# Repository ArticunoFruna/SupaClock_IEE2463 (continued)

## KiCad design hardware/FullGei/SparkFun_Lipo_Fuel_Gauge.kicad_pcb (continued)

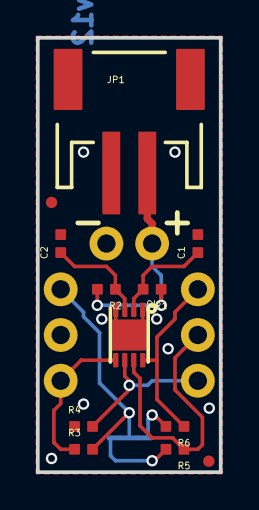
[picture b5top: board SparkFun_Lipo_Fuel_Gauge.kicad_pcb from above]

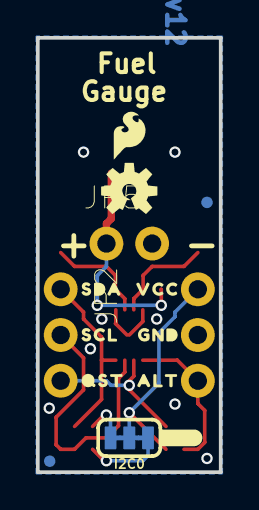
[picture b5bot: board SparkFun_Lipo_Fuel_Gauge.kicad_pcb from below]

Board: 2 copper layers, 10.2 x 24.1 mm, 29 parts (15 on the bottom side), 11 nets.

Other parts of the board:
U$2: SDA0
U$3: SCL0
U$4: QST0
U$5: VCC0
U$6: GND0
U$7: ALT0
U$8: #I2C#0

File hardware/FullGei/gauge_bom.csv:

"Reference","Value","Footprint"
"C1","1.0uF","SparkFun_Lipo_Fuel_Gauge:0402-TIGHT"
"C2","10nF","SparkFun_Lipo_Fuel_Gauge:0402-TIGHT"
"FRAME1","FRAME-LETTER","SparkFun_Lipo_Fuel_Gauge:CREATIVE_COMMONS"
"I2C0","JUMPER-SMT_3_2-NC_TRACE_SILK","SparkFun_Lipo_Fuel_Gauge:SMT-JUMPER_3_2-NC_TRACE_SILK"
"JP1","input","SparkFun_Lipo_Fuel_Gauge:JST-2-SMD"
"JP2","CONN_031X03_NO_SILK","SparkFun_Lipo_Fuel_Gauge:1X03_NO_SILK"
"JP3","SFE_LOGO_FLAME.1_INCH","SparkFun_Lipo_Fuel_Gauge:SFE_LOGO_FLAME_.1"
"JP4","CONN_031X03_NO_SILK","SparkFun_Lipo_Fuel_Gauge:1X03_NO_SILK"
"JP5","CONN_021X02_NO_SILK","SparkFun_Lipo_Fuel_Gauge:1X02_NO_SILK"
"JP6","FIDUCIALUFIDUCIAL","SparkFun_Lipo_Fuel_Gauge:FIDUCIAL-MICRO"
"JP7","FIDUCIALUFIDUCIAL","SparkFun_Lipo_Fuel_Gauge:FIDUCIAL-MICRO"
"JP8","FIDUCIALUFIDUCIAL","SparkFun_Lipo_Fuel_Gauge:FIDUCIAL-MICRO"
"JP9","FIDUCIALUFIDUCIAL","SparkFun_Lipo_Fuel_Gauge:FIDUCIAL-MICRO"
"LOGO1","SFE_LOGO_NAME_FLAMEBLANK","SparkFun_Lipo_Fuel_Gauge:BLANK"
"R1","1k","SparkFun_Lipo_Fuel_Gauge:0402-TIGHT"
"R2","100","SparkFun_Lipo_Fuel_Gauge:0402-TIGHT"
"R3","2.2k","SparkFun_Lipo_Fuel_Gauge:0402-TIGHT"
"R4","2.2k","SparkFun_Lipo_Fuel_Gauge:0402-TIGHT"
"R5","2.2k","SparkFun_Lipo_Fuel_Gauge:0402-TIGHT"
"R6","2.2k","SparkFun_Lipo_Fuel_Gauge:0402-TIGHT"
"U$1","OSHW-LOGOS","SparkFun_Lipo_Fuel_Gauge:OSHW-LOGO-S"
"U2","MAX1704X","SparkFun_Lipo_Fuel_Gauge:TDFN-8"

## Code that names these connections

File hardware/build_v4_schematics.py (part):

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U1_X, U1_Y = 160.0, 100.0
m.place("U1", "XIAO-ESP32-S3", "Seeed_Studio_XIAO_Series:XIAO-ESP32-S3-SMD", "Seeed_Studio_XIAO_Footprints:XIAO-ESP32-S3-SMD", U1_X, U1_Y)

m.label_pin("U1", "Seeed_Studio_XIAO_Series:XIAO-ESP32-S3-SMD", U1_X, U1_Y, 0, "1", "ECG_OUT")
m.label_pin("U1", "Seeed_Studio_XIAO_Series:XIAO-ESP32-S3-SMD", U1_X, U1_Y, 0, "2", "ECG_SDN")
m.label_pin("U1", "Seeed_Studio_XIAO_Series:XIAO-ESP32-S3-SMD", U1_X, U1_Y, 0, "3", "BLK_PWM")
m.label_pin("U1", "Seeed_Studio_XIAO_Series:XIAO-ESP32-S3-SMD", U1_X, U1_Y, 0, "4", "SPI_DC")
m.label_pin("U1", "Seeed_Studio_XIAO_Series:XIAO-ESP32-S3-SMD", U1_X, U1_Y, 0, "5", "I2C_SDA")
m.label_pin("U1", "Seeed_Studio_XIAO_Series:XIAO-ESP32-S3-SMD", U1_X, U1_Y, 0, "6", "I2C_SCL")
m.label_pin("U1", "Seeed_Studio_XIAO_Series:XIAO-ESP32-S3-SMD", U1_X, U1_Y, 0, "7", "BTN_NEXT")
m.label_pin("U1", "Seeed_Studio_XIAO_Series:XIAO-ESP32-S3-SMD", U1_X, U1_Y, 0, "8", "SPI_CS")
m.label_pin("U1", "Seeed_Studio_XIAO_Series:XIAO-ESP32-S3-SMD", U1_X, U1_Y, 0, "9", "SPI_SCK")
m.label_pin("U1", "Seeed_Studio_XIAO_Series:XIAO-ESP32-S3-SMD", U1_X, U1_Y, 0, "10", "BTN_SELECT")
m.label_pin("U1", "Seeed_Studio_XIAO_Series:XIAO-ESP32-S3-SMD", U1_X, U1_Y, 0, "11", "SPI_MOSI")
m.power_pin("U1", "Seeed_Studio_XIAO_Series:XIAO-ESP32-S3-SMD", U1_X, U1_Y, 0, "12", "+3V3")
m.power_pin("U1", "Seeed_Studio_XIAO_Series:XIAO-ESP32-S3-SMD", U1_X, U1_Y, 0, "13", "GND")
m.power_pin("U1", "Seeed_Studio_XIAO_Series:XIAO-ESP32-S3-SMD", U1_X, U1_Y, 0, "32", "+BATT")
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# 2. SELECT button (SW1) & NEXT button (SW2)
SW1_X, SW1_Y = 90.0, 60.0
m.place("SW1", "SELECT", "Switch:SW_Push", "SupaClock_Custom:SW_Tactile_Side_3.5x7.8mm", SW1_X, SW1_Y)
m.label_pin("SW1", "Switch:SW_Push", SW1_X, SW1_Y, 0, "1", "BTN_SELECT")
m.power_pin("SW1", "Switch:SW_Push", SW1_X, SW1_Y, 0, "2", "GND")

C4_X, C4_Y = 70.0, 60.0
m.place("C4", "100nF", "Device:C", "Capacitor_SMD:C_0805_2012Metric_Pad1.18x1.45mm_HandSolder", C4_X, C4_Y)
m.label_pin("C4", "Device:C", C4_X, C4_Y, 0, "1", "BTN_SELECT")
m.power_pin("C4", "Device:C", C4_X, C4_Y, 0, "2", "GND")

R3_X, R3_Y = 70.0, 45.0
m.place("R3", "10k", "Device:R", "Resistor_SMD:R_0805_2012Metric_Pad1.20x1.40mm_HandSolder", R3_X, R3_Y)
m.label_pin("R3", "Device:R", R3_X, R3_Y, 0, "1", "BTN_SELECT")
m.power_pin("R3", "Device:R", R3_X, R3_Y, 0, "2", "+3V3")

SW2_X, SW2_Y = 90.0, 90.0
m.place("SW2", "NEXT", "Switch:SW_Push", "SupaClock_Custom:SW_Tactile_Side_3.5x7.8mm", SW2_X, SW2_Y)
m.label_pin("SW2", "Switch:SW_Push", SW2_X, SW2_Y, 0, "1", "BTN_NEXT")
m.power_pin("SW2", "Switch:SW_Push", SW2_X, SW2_Y, 0, "2", "GND")

C5_X, C5_Y = 70.0, 90.0
m.place("C5", "100nF", "Device:C", "Capacitor_SMD:C_0805_2012Metric_Pad1.18x1.45mm_HandSolder", C5_X, C5_Y)
m.label_pin("C5", "Device:C", C5_X, C5_Y, 0, "1", "BTN_NEXT")
m.power_pin("C5", "Device:C", C5_X, C5_Y, 0, "2", "GND")

R4_X, R4_Y = 70.0, 75.0
m.place("R4", "10k", "Device:R", "Resistor_SMD:R_0805_2012Metric_Pad1.20x1.40mm_HandSolder", R4_X, R4_Y)
m.label_pin("R4", "Device:R", R4_X, R4_Y, 0, "1", "BTN_NEXT")
m.power_pin("R4", "Device:R", R4_X, R4_Y, 0, "2", "+3V3")

# 3. I2C pull-ups R1, R2 (4.7k)
R1_X, R1_Y = 70.0, 110.0
m.place("R1", "4.7k", "Device:R", "Resistor_SMD:R_0805_2012Metric_Pad1.20x1.40mm_HandSolder", R1_X, R1_Y)
m.label_pin("R1", "Device:R", R1_X, R1_Y, 0, "1", "I2C_SDA")
m.power_pin("R1", "Device:R", R1_X, R1_Y, 0, "2", "+3V3")

R2_X, R2_Y = 70.0, 125.0
m.place("R2", "4.7k", "Device:R", "Resistor_SMD:R_0805_2012Metric_Pad1.20x1.40mm_HandSolder", R2_X, R2_Y)
m.label_pin("R2", "Device:R", R2_X, R2_Y, 0, "1", "I2C_SCL")
m.power_pin("R2", "Device:R", R2_X, R2_Y, 0, "2", "+3V3")

# 4. MAX17048 Fuel Gauge (U2) at (260, 60)
U2_X, U2_Y = 260.0, 60.0
m.place("U2", "MAX17048", "SparkFun_Lipo_Fuel_Gauge-eagle-import:MAX1704X", "SupaClock_Custom:MAX17048_WDFN8_HandSolder", U2_X, U2_Y)
m.power_pin("U2", "SparkFun_Lipo_Fuel_Gauge-eagle-import:MAX1704X", U2_X, U2_Y, 0, "1", "GND") # CTG
m.label_pin("U2", "SparkFun_Lipo_Fuel_Gauge-eagle-import:MAX1704X", U2_X, U2_Y, 0, "2", "CELL_FILT")
m.label_pin("U2", "SparkFun_Lipo_Fuel_Gauge-eagle-import:MAX1704X", U2_X, U2_Y, 0, "3", "VDD_FILT")
m.power_pin("U2", "SparkFun_Lipo_Fuel_Gauge-eagle-import:MAX1704X", U2_X, U2_Y, 0, "4", "GND")
m.label_pin("U2", "SparkFun_Lipo_Fuel_Gauge-eagle-import:MAX1704X", U2_X, U2_Y, 0, "5", "FG_ALT")
m.label_pin("U2", "SparkFun_Lipo_Fuel_Gauge-eagle-import:MAX1704X", U2_X, U2_Y, 0, "6", "FG_QST")
m.label_pin("U2", "SparkFun_Lipo_Fuel_Gauge-eagle-import:MAX1704X", U2_X, U2_Y, 0, "7", "I2C_SCL")
m.label_pin("U2", "SparkFun_Lipo_Fuel_Gauge-eagle-import:MAX1704X", U2_X, U2_Y, 0, "8", "I2C_SDA")
m.power_pin("U2", "SparkFun_Lipo_Fuel_Gauge-eagle-import:MAX1704X", U2_X, U2_Y, 0, "EP", "GND")

# R_FG1 (1k 0805)
RFG1_X, RFG1_Y = 230.0, 35.0
m.place("R_FG1", "1k", "Device:R", "Resistor_SMD:R_0805_2012Metric_Pad1.20x1.40mm_HandSolder", RFG1_X, RFG1_Y)
m.label_pin("R_FG1", "Device:R", RFG1_X, RFG1_Y, 0, "1", "CELL_FILT")
m.power_pin("R_FG1", "Device:R", RFG1_X, RFG1_Y, 0, "2", "+BATT")

# C_FG1 (1uF 0805)
CFG1_X, CFG1_Y = 230.0, 50.0
m.place("C_FG1", "1uF", "Device:C", "Capacitor_SMD:C_0805_2012Metric_Pad1.18x1.45mm_HandSolder", CFG1_X, CFG1_Y)
m.label_pin("C_FG1", "Device:C", CFG1_X, CFG1_Y, 0, "1", "CELL_FILT")
m.power_pin("C_FG1", "Device:C", CFG1_X, CFG1_Y, 0, "2", "GND")

# R_FG2 (100 ohm 0805)
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# R_FG_ALT (10k 0805 pull-up on ALT)
RFGALT_X, RFGALT_Y = 290.0, 45.0
m.place("R_FG_ALT", "10k", "Device:R", "Resistor_SMD:R_0805_2012Metric_Pad1.20x1.40mm_HandSolder", RFGALT_X, RFGALT_Y)
m.label_pin("R_FG_ALT", "Device:R", RFGALT_X, RFGALT_Y, 0, "1", "FG_ALT")
m.power_pin("R_FG_ALT", "Device:R", RFGALT_X, RFGALT_Y, 0, "2", "+3V3")

# R_FG_QST (10k 0805 pull-down on QST)
RFGQST_X, RFGQST_Y = 290.0, 65.0
m.place("R_FG_QST", "10k", "Device:R", "Resistor_SMD:R_0805_2012Metric_Pad1.20x1.40mm_HandSolder", RFGQST_X, RFGQST_Y)
m.label_pin("R_FG_QST", "Device:R", RFGQST_X, RFGQST_Y, 0, "1", "FG_QST")
m.power_pin("R_FG_QST", "Device:R", RFGQST_X, RFGQST_Y, 0, "2", "GND")

# 5. JST Battery Connector (J_BAT) at (260, 110)
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Q1_X, Q1_Y = 100.0, 220.0
m.place("Q1", "2N7002", "Transistor_FET:2N7000", "Package_TO_SOT_SMD:SOT-23_Handsoldering", Q1_X, Q1_Y)
m.power_pin("Q1", "Transistor_FET:2N7000", Q1_X, Q1_Y, 0, "1", "GND")       # Source
m.label_pin("Q1", "Transistor_FET:2N7000", Q1_X, Q1_Y, 0, "2", "BLK_PWM")    # Gate
m.label_pin("Q1", "Transistor_FET:2N7000", Q1_X, Q1_Y, 0, "3", "LED_K")      # Drain

# R_GATE (10k 0805) pull-down for Gate of Q1
RGATE_X, RGATE_Y = 100.0, 195.0
m.place("R_GATE", "10k", "Device:R", "Resistor_SMD:R_0805_2012Metric_Pad1.20x1.40mm_HandSolder", RGATE_X, RGATE_Y)
m.label_pin("R_GATE", "Device:R", RGATE_X, RGATE_Y, 0, "1", "BLK_PWM")
m.power_pin("R_GATE", "Device:R", RGATE_X, RGATE_Y, 0, "2", "GND")

# R_LEDA (22R 0805) current limiting resistor
RLEDA_X, RLEDA_Y = 120.0, 195.0
m.place("R_LEDA", "22", "Device:R", "Resistor_SMD:R_0805_2012Metric_Pad1.20x1.40mm_HandSolder", RLEDA_X, RLEDA_Y)
m.power_pin("R_LEDA", "Device:R", RLEDA_X, RLEDA_Y, 0, "1", "+3V3")
m.label_pin("R_LEDA", "Device:R", RLEDA_X, RLEDA_Y, 0, "2", "LED_A")

# FPC Configuration Pull-ups: R_IM (10k), R_RD (10k), R_RST (10k)
# R_IM
RIM_X, RIM_Y = 120.0, 240.0
m.place("R_IM", "10k", "Device:R", "Resistor_SMD:R_0805_2012Metric_Pad1.20x1.40mm_HandSolder", RIM_X, RIM_Y)
m.label_pin("R_IM", "Device:R", RIM_X, RIM_Y, 0, "1", "IM_HI")
m.power_pin("R_IM", "Device:R", RIM_X, RIM_Y, 0, "2", "+3V3")

# R_RD
RRD_X, RRD_Y = 135.0, 240.0
m.place("R_RD", "10k", "Device:R", "Resistor_SMD:R_0805_2012Metric_Pad1.20x1.40mm_HandSolder", RRD_X, RRD_Y)
m.label_pin("R_RD", "Device:R", RRD_X, RRD_Y, 0, "1", "RD_HI")
m.power_pin("R_RD", "Device:R", RRD_X, RRD_Y, 0, "2", "+3V3")

# R_RST
RRST_X, RRST_Y = 150.0, 240.0
m.place("R_RST", "10k", "Device:R", "Resistor_SMD:R_0805_2012Metric_Pad1.20x1.40mm_HandSolder", RRST_X, RRST_Y)
m.label_pin("R_RST", "Device:R", RRST_X, RRST_Y, 0, "1", "RST_HI")
m.power_pin("R_RST", "Device:R", RRST_X, RRST_Y, 0, "2", "+3V3")

# C_RST (100nF 0805) auto-reset capacitor
CRST_X, CRST_Y = 150.0, 260.0
m.place("C_RST", "100nF", "Device:C", "Capacitor_SMD:C_0805_2012Metric_Pad1.18x1.45mm_HandSolder", CRST_X, CRST_Y)
m.label_pin("C_RST", "Device:C", CRST_X, CRST_Y, 0, "1", "RST_HI")
m.power_pin("C_RST", "Device:C", CRST_X, CRST_Y, 0, "2", "GND")

# C_DISP1 (10uF) & C_DISP2 (100nF) for display decoupling
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m.power_pin("J_IMU", "Connector_Generic:Conn_01x07", JIMU_X, JIMU_Y, 0, "1", "+3V3")   # VCC
m.label_pin("J_IMU", "Connector_Generic:Conn_01x07", JIMU_X, JIMU_Y, 0, "2", "IMU_INT1")
m.power_pin("J_IMU", "Connector_Generic:Conn_01x07", JIMU_X, JIMU_Y, 0, "3", "GND")   # GND
m.label_pin("J_IMU", "Connector_Generic:Conn_01x07", JIMU_X, JIMU_Y, 0, "4", "I2C_SCL")
m.label_pin("J_IMU", "Connector_Generic:Conn_01x07", JIMU_X, JIMU_Y, 0, "5", "I2C_SDA")
m.power_pin("J_IMU", "Connector_Generic:Conn_01x07", JIMU_X, JIMU_Y, 0, "6", "+3V3")   # SA0 tied to 3.3V
m.power_pin("J_IMU", "Connector_Generic:Conn_01x07", JIMU_X, JIMU_Y, 0, "7", "GND")   # Tie last pin to GND
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
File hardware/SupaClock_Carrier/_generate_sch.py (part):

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# MICROCONTROLADOR: Seeed XIAO ESP32-S3 (símbolo DIP oficial de Seeed)
# ============================================================
# Pin map XIAO ESP32-S3 v1.2 (post-feedback - usa BMS interno del XIAO):
#   1 = D0  / GPIO1  / ADC1_CH0 -> ECG_OUT      (analog input)
#   2 = D1  / GPIO2             -> ECG_SDN      (digital out, controla AD8232 SDN)
#   3 = D2  / GPIO3             -> BLK_PWM      (PWM out, controla backlight ST7789)
#   4 = D3  / GPIO4             -> SPI_DC
#   5 = D4  / GPIO5  / I2C SDA  -> I2C_SDA
#   6 = D5  / GPIO6  / I2C SCL  -> I2C_SCL
#   7 = D6  / GPIO43 / UART_TX  -> BTN_NEXT
#   8 = D7  / GPIO44 / UART_RX  -> SPI_CS
#   9 = D8  / GPIO7  / SCK      -> SPI_SCK
#  10 = D9  / GPIO8  / MISO     -> BTN_SELECT
#  11 = D10 / GPIO9  / MOSI     -> SPI_MOSI
#  12 = 3V3 (salida del buck SY8089 interno -> rail +3V3 del carrier)
#  13 = GND
#  14 = VBUS / 5V              -> NC (USB del XIAO se usa solo para carga + dev)
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    x=200,
    y=50,
    rot=0,
    pin_nets={1: "+3V3", 2: "I2C_SDA"},
)
add(
    "R2",
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    x=215,
    y=50,
    rot=0,
    pin_nets={1: "+3V3", 2: "I2C_SCL"},
)


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    x=145,
    y=145,
    rot=0,
    pin_nets={1: "+3V3", 2: "SPI_RES"},
)
add(
    "C6",
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    x=155,
    y=145,
    rot=0,
    pin_nets={1: "SPI_RES", 2: "GND"},
)


# ============================================================
# AD8232 SparkFun-style (red PCB con jack 3.5mm)
# - 6-pin header: GND, 3V3, OUTPUT, LO-, LO+, SDN
# - 3 pads aparte: RA, LA, RL (alternativos al jack 3.5mm)
# ============================================================
add(
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    pin_nets={
        1: "GND",
        2: "+3V3",      # 3.3V
        3: "ECG_OUT",   # OUTPUT (analog -> ADC del XIAO GPIO1)
        4: "_NC_",      # LO-  (leads-off detect, no usado en v1)
        5: "_NC_",      # LO+  (leads-off detect, no usado en v1)
        6: "ECG_SDN",   # SDN controlado por XIAO D1 - HIGH=activo, LOW=shutdown
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    x=160,
    y=160,
    rot=0,
    pin_nets={1: "ECG_RA"},
    footprint="SupaClock_Custom:M3_Electrode_Pad",
)
add(
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    x=160,
    y=175,
    rot=0,
    pin_nets={1: "ECG_LA"},
    footprint="SupaClock_Custom:M3_Electrode_Pad",
)
add(
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    x=160,
    y=190,
    rot=0,
    pin_nets={1: "ECG_RL"},
    footprint="SupaClock_Custom:M3_Electrode_Pad",
)

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    x=280,
    y=160,
    rot=0,
    pin_nets={1: "BTN_SELECT", 2: "GND"},
)
# SW2: NEXT
add(
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    x=300,
    y=160,
    rot=0,
    pin_nets={1: "BTN_NEXT", 2: "GND"},
)
# Pull-ups botones (opcionales — XIAO ESP32-S3 tiene pull-ups internos pero externos son robustez extra)
add(
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    x=280,
    y=140,
    rot=0,
    pin_nets={1: "+3V3", 2: "BTN_SELECT"},
    dnp=True,  # default not stuffed — usar pull-up interno
)
add(
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    x=300,
    y=140,
    rot=0,
    pin_nets={1: "+3V3", 2: "BTN_NEXT"},
    dnp=True,
)
# Capacitores de debounce (opcionales)
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    x=280,
    y=175,
    rot=0,
    pin_nets={1: "BTN_SELECT", 2: "GND"},
    dnp=True,
)
add(
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    x=300,
    y=175,
    rot=0,
    pin_nets={1: "BTN_NEXT", 2: "GND"},
    dnp=True,
)

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
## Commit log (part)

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2026-03-13 Init: Arquitectura base del proyecto y configuración PIO
2026-03-13 Build: Añadir estructura de carpetas para hardware y documentos
2026-03-20 Añadidos documentos, diagramas de bloque, etc.
2026-03-26 Agregado el informe de planificación
2026-03-26 Setup project structure
2026-03-29 feat: implement I2C read/write primitives, add BLE telemetry module, and integrate MAX30205 sensor task
2026-03-30 feat: implement modular test environment with isolated build targets and add peripheral driver test suite
2026-03-31 feat: integrate espressif__esp_jpeg component and update JPEGDEC_driver examples and configurations
2026-04-01 refactor: inherit build flags in platformio.ini and update JPEGDraw comments
2026-04-01 docs: add architectural and conceptual documentation for SupaClock project
2026-04-01 Actualizada la guía para conceptos básicos
2026-04-01 docs: add introductory guide for new project contributors
2026-04-08 docs: add project documentation, presentation files, and hardware history tracking
2026-04-08 Comentarios de los códigos asociados al avance 5%
2026-04-08 chore: migrate presentation theme to focus and update project documentation and driver source files
2026-04-18 feat: integrate BMI160 driver, add step algorithm, update documentation, and expand testing and simulation tools.
2026-04-20 refactor: remove esp_jpeg component and update telemetry appearance configuration
2026-04-20 feat: integrate LVGL component and modularize step_algorithm and ble_telemetry using CMakeLists registration
2026-04-22 lala
2026-04-23 refactor: update BLE telemetry protocol, add performance testing scripts, and manage tool output files.
2026-04-24 Refactor code structure for improved readability and maintainability
2026-04-28 Informe 25%, PWM para pantalla, pruebas
2026-04-29 Presentación preeliminar 25%
2026-04-29 Add Focus Beamer Theme and Presentation Files
    - Introduced new Beamer theme files: beamerthemefocus.sty and beamerouterthemefocus.sty for enhanced presentation styling.
    - Created a new LaTeX presentation (presentacion.tex) for the "SupaClock" project, including sections on hardware, firmware, and future plans.
    - Added a Python script (supaclock_raw_ppg.py) for capturing raw PPG data from the MAX30102 sensor and generating comparative plots.
    - Generated a new PDF presentation file (presentacion.pdf) based on the LaTeX source.
2026-04-30 feat: improve MAX17048 stability with EMA filtering, hibernate configuration, and POR handling while increasing AD8232 buffer size
2026-04-30 Presentación con nuevos diagramas y figura PCB
2026-04-30 Avances en presentación (diagramas y figuras)
2026-04-30 Ajustes a diagramas y slides PPT
2026-04-30 feat: add ECG signal analysis tools, documentation, and hardware test utilities
2026-04-30 docs: update power consumption chart data and correct LDO regulator model name in presentation files
2026-04-30 Add PC simulator files with SDL support and initial UI implementation
    - Created lv_drv_conf.h for SDL configuration.
    - Added platformio.ini for build environment setup.
    - Implemented main.c with a complete UI for health monitoring, including screens for home, bio, HR spot, ECG, menu, mode, and settings.
    - Integrated sensor data simulation and button handling for navigation.
    - Utilized LVGL for GUI rendering and SDL for display management.
2026-05-03 Informe2
2026-05-04 Informe 2: Cambios de redacción, análisis comparativo frente a la industria y modificación de algunas pruebas
2026-05-05 docs: update documentation for final validation set-up, Pan-Tompkins algorithm progress, and project roadmap
2026-05-05 cambio carta gantt
2026-05-05 Add TP4056 schematic and USB Micro-B footprint
    - Created a new schematic file for the TP4056 circuit in KiCad format, including components such as capacitors, resistors, LEDs, connectors, and the TP4056 IC itself.
    - Added a footprint for the USB Micro-B connector, detailing its dimensions and pin configurations, suitable for surface mount applications.
2026-05-05 Correcciones de imágenes del informe de 25%
2026-05-12 Add symbol library for Seeed Studio XIAO series MCU modules
2026-05-12 Remove duplicate signal diagram image files
2026-05-12 feat: Update SupaClock Carrier project settings and add tuning profiles
    - Disabled default application for footprint barcodes and dimensions.
    - Introduced new warnings for footprint symbol field mismatches and missing tuning profiles.
    - Added support for tuning profiles in design settings.
    - Updated IPC2581 settings with a new schematic revision field.
    - Enhanced error handling for various design rule checks.
    - Incremented project version to 5 and added tuning profiles metadata.
2026-05-13 refactor: update component placement, replace automation scripts with lpkf rules, and add drc report
2026-05-13 Add script to fix THT pad sizes for LPKF CNC fabrication
    - Introduced `fix_pads_lpkf.py` to enlarge THT pad annular rings to meet LPKF ProtoMat S64 minimum requirements.
    - Implemented board-level design rules for clearance, track width, and via dimensions.
    - Fixed THT pad sizes and ensured pad shapes are consistent.
    - Included verification checks for pad sizes and design rules after modifications.
2026-05-15 Update design rule severities in SupaClock_Carrier project
    - Changed clearance rule severity from error to ignore
    - Changed nonmirrored text on back layer rule severity from warning to ignore
    - Updated silk over copper and silk overlap rule severities from warning to ignore
2026-05-15 Update design rules and footprint for MAX30102
    - Increased minimum through hole diameter from 0.8mm to 1.0mm.
    - Adjusted minimum via annular width from 0.6mm to 0.4mm and minimum via diameter from 2.0mm to 1.8mm.
    - Modified the footprint for MAX30102_Castellated_1x4 by changing the yard dimensions and adding additional lines for improved clarity.
2026-05-15 Modelo de ML
2026-05-15 Add DRC JSON files for SupaClock Carrier: drc_post_relax.json and drc_post_thtswap.json
    - Created drc_post_relax.json with 509 violations and warnings related to thermal relief, text dimensions, and footprint mismatches.
    - Created drc_post_thtswap.json with 653 violations and warnings, including unconnected items, hole size issues, and silkscreen clearance violations.
    - Both files include ignored checks and are formatted according to the KiCad DRC schema.
2026-05-20 Add DRC configuration file for SupaClock Carrier with detailed violation reports
2026-05-23 feat(mechanical): add SupaClock V2 concept design with enhanced aesthetics
    - Introduced `supaclock_v2_concept.scad` for visual representation of the new design.
    - Added `supaclock_v2_dimensions.md` detailing critical dimensions for Fusion 360 reconstruction.
    - Created `supaclock_v2_top_case.scad` for the functional top case with improved features.
    - Generated corresponding STL files for both concept and top case.
    - Updated partitioning for ESP32-C3 SuperMini in `partitions_c3.csv`.
    - Migration to ESP32 S3
2026-05-25 Add schematic generation and symbol extraction for SupaClock_Display_Adapter
    - Implemented build_schematic.py to generate the SupaClock_Display_Adapter.kicad_sch file from a predefined library of symbols, including placement and wiring of components.
    - Created extract_symbols.sh to extract necessary symbols from KiCad's symbol libraries and format them for the schematic.
    - Added fp-lib-table and sym-lib-table files to define custom footprints and symbol libraries for the project.
2026-05-25 nurvos cambios
2026-05-25 ultimos cambios
2026-05-26 Add new STL file for Supaclock V2 top case
2026-05-26 Datos ML
2026-05-26 Ajustes a modelo de ML para S3 y entrenamiento con datos medidos
2026-05-26 Agregar presentacion Entrega 3
2026-05-28 Cambios en la presentación y modelo ML
2026-05-28 Diagrama de bloques E3
2026-05-28 Add UI font and theme management with NVS persistence
    - Introduced custom UI fonts in `ui_fonts.h` for better text rendering.
    - Created `ui_theme` module with color themes, allowing users to switch themes.
    - Implemented NVS storage for persisting the active theme across sessions.
    - Added functionality to retrieve and set themes, including a count of available themes.
    - Updated `test_general.c` to enhance screen transition animations.
2026-05-28 Add header file for Supaclock UI module
    - Introduced `supaclock_ui.h` to define the UI interface for the Supaclock application.
    - Added function prototypes for UI initialization, action configuration, button event handling, and periodic UI updates.
    - Defined a structure for UI actions to handle power off and battery reset events.
2026-05-28 Datos ML, entrenamiento y detalles presentacion
2026-06-01 docs(Entrega3): convert markdown report to LaTeX (main.tex + ref.bib)
2026-06-02 Refactor code structure and remove redundant sections for improved readability and maintainability
2026-06-02 Explicación ML presentación
2026-06-15 Add large image files for project documentation
    - Added carcasas.png (7344 KB) to the Entrega3 documentation.
    - Added prototipopcb.png (8773 KB) to the Entrega3 documentation.
2026-06-15 Add initial web files for supaclock_app including index.html and manifest.json
    - Created index.html with necessary meta tags and base href for Flutter web app.
    - Added manifest.json for PWA support with app details and icons.
2026-06-19 Refactor code structure and remove redundant changes
2026-06-19 Cambios de Machine Learning y entrenamiento HAR
2026-06-25 docs: add entrega4 presentations
2026-06-25 feat: Add firmware handoff documentation and new HAR replay tool
    - Created `firmware_handoff_har.md` to outline app changes for firmware coordination, including TLV consumption, IMU cadence, and required artifacts.
    - Introduced `har_replay.py` script to re-run the HAR model on recorded sessions, normalizing IMU data and generating confusion matrices for model validation against manual labels.
    - Updated documentation to reflect changes in data handling and model inference processes.
2026-06-25 mechanical: adjust v2 case ports
2026-06-25 Presentacion 4
